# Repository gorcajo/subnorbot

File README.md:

# Subnorbot

In 2013 two friends and me participated in a robot-sumo contest (Alcabot) while we were still students.

This repository contains the soruce and hardware schematics we used to develop the robot. It is based on Arduino Uno.

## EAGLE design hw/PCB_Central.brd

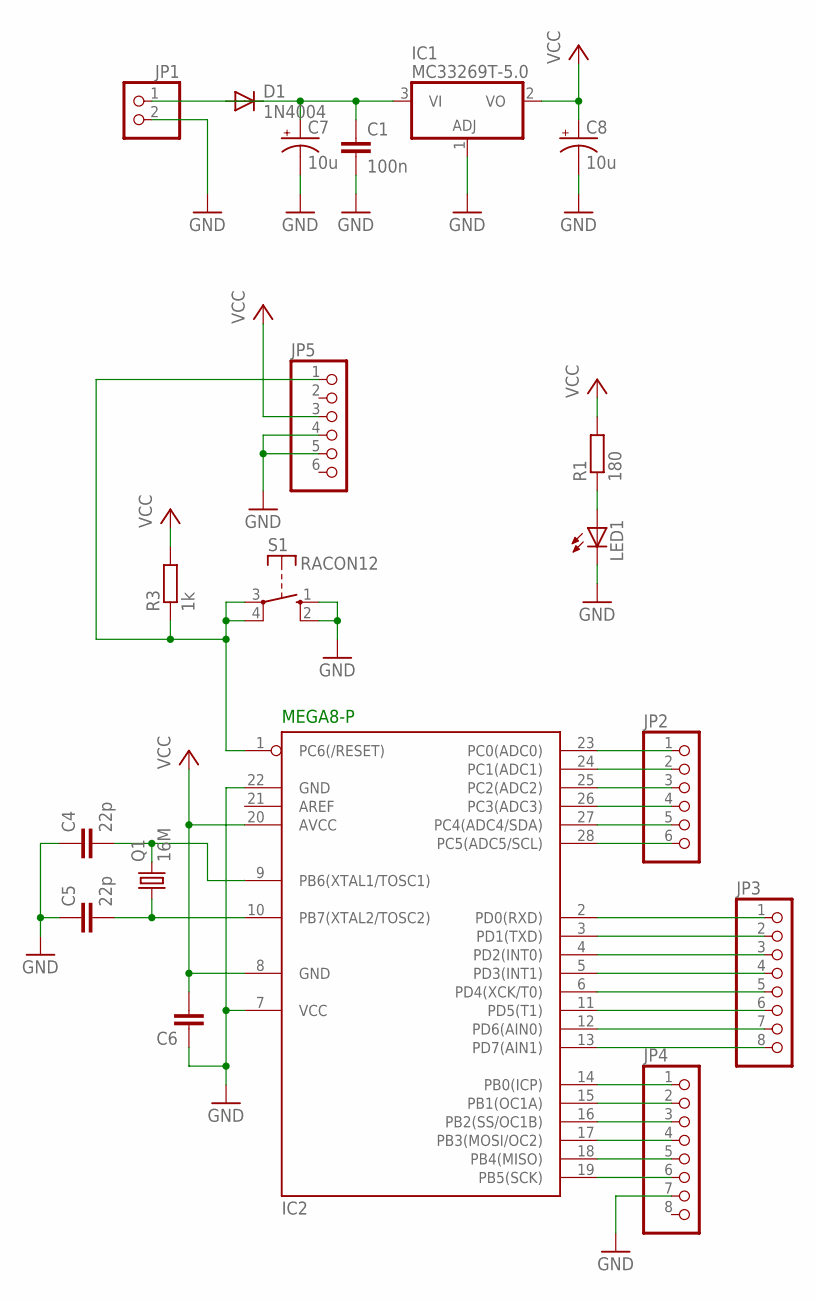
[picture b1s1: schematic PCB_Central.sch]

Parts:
C1: 100n; C2.5-3
C4, C5: 22p; C2.5-3
C6: C2,5-3; C2.5-3
C7, C8: 10u; E5-13
D1: 1N4004; DO41-10
IC1: MC33269T-5.0; TO220V
IC2: MEGA8-P; DIL28-3
JP1: PINHD-1X2; 1X02
JP2, JP5: PINHD-1X6; 1X06
JP3, JP4: PINHD-1X8; 1X08
LED1: LED5MM
Q1: 16M; HC49/S
R1: 180; 0207/12
R3: 1k; 0207/12
S1: RACON12

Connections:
GND: C1.2, C4.1, C5.1, C6.1, C7.-, C8.-, IC1.1 (ADJ), IC2.7 (VCC), IC2.22 (GND), JP1.2, JP4.7, JP5.4, JP5.5, LED1.K (C), S1.1 (S), S1.2 (S)
unnamed: LED1.A, R1.1
unnamed: C1.1, C7.+, D1.A, D1.C, IC1.3 (VI), JP1.1
unnamed: IC2.1 (PC6(/RESET)), JP5.1, R3.1, S1.3, S1.4
unnamed: IC2.14 (PB0(ICP)), JP4.1
unnamed: IC2.15 (PB1(OC1A)), JP4.2
unnamed: IC2.16 (PB2(SS/OC1B)), JP4.3
unnamed: IC2.17 (PB3(MOSI/OC2)), JP4.4
unnamed: IC2.18 (PB4(MISO)), JP4.5
unnamed: IC2.19 (PB5(SCK)), JP4.6
unnamed: C4.2, IC2.9 (PB6(XTAL1/TOSC1)), Q1.2
unnamed: C5.2, IC2.10 (PB7(XTAL2/TOSC2)), Q1.1
unnamed: IC2.23 (PC0(ADC0)), JP2.1
unnamed: IC2.24 (PC1(ADC1)), JP2.2
unnamed: IC2.25 (PC2(ADC2)), JP2.3
unnamed: IC2.26 (PC3(ADC3)), JP2.4
unnamed: IC2.27 (PC4(ADC4/SDA)), JP2.5
unnamed: IC2.28 (PC5(ADC5/SCL)), JP2.6
unnamed: IC2.2 (PD0(RXD)), JP3.1
unnamed: IC2.3 (PD1(TXD)), JP3.2
unnamed: IC2.4 (PD2(INT0)), JP3.3
unnamed: IC2.5 (PD3(INT1)), JP3.4
unnamed: IC2.6 (PD4(XCK/T0)), JP3.5
unnamed: IC2.11 (PD5(T1)), JP3.6
unnamed: IC2.12 (PD6(AIN0)), JP3.7
unnamed: IC2.13 (PD7(AIN1)), JP3.8
VCC: C6.2, C8.+, IC1.2 (VO), IC2.8 (GND), IC2.20 (AVCC), JP5.3, R1.2, R3.2

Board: 2 copper layers, 19 parts (0 on the bottom side), 27 nets, no tracks yet.

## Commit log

2013-03-07 Commit inicial.
2013-03-07 Prueba 1
2013-03-07 Prueba 2
2013-03-07 Prueba 3
2013-03-11 Prueba 4
2013-03-11 Prueba 5
2013-03-11 cacaculopedopis
2013-03-11 mi pene
2013-03-11 Limpieza de ficheros guarros para pruebas.
2013-03-18 - Nueva carpeta de recursos donde meter links, instrucciones, manuales, herramientas... - Fichero de texto con las instrucciones para usar el programador AVRISP MKII de Atmel con Arduino.
2013-03-18 Agregados los drivers para Windows del AVRISPmk2 en /recursos/.
2013-03-18 Pequeña nota en el uso del AVRISPmk2.
2013-03-18 añadido datasheet atmega328p
2013-03-19 - Nueva carpeta de /recursos/ con lo siguiente: -- Añadida una propuesta para la estructura sw. -- Añadida una propuesta acerca de estándares de programación. - Añadido un fichero sobre links de inte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
2013-03-19 - Nueva carpeta, /doc/ - Propuesta de estructura de sw en /doc/ - Propuesta de estándares de programacion en /doc/ - Fichero con links de interes en /recursos/
2013-03-21 Estructura base del SW. - Descrita en subnorbot.h la estructura sw que existe hasta el momento. - Implementado el metodo setSnifers() en sense.cpp. - Modificado sw.ino para incluir las librerias que 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
2013-03-24 Método SubnorBot.initializa() finalizado, a falta de más operaciones que realizar o nuevas propiedades que inicializar. Creadas nuevas macros en subnorbot.h: constantes acerca del hardware, como los 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
2013-03-24 Método SubnorBot.move() terminado. Añadido nuevo convenio en /doc/estandaresProgramacion.txt Mejorado SubnorBot.initialize() Añadidos algunos prototipos de funciones en resolve.cpp
2013-03-24 Ahora las funciones de la IA utilizadas en resolve.cpp son métodos dentro de la clase SubnorBot. A partir de ahora si fuera necesario añadir más métodos se hará dentro de su "apartado" correspondient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
2013-03-24 Implementado el esqueleto de una primera version de la maquina de estados de la IA en resolve(). Implementados los métodos básicos de IA rotate(), pivot(), approach() y charge(). Eliminación de algun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
2013-03-24 Nueva constante en subnorbot.h: ENGINES_SPEED_CORRECTION. Cambios menores.
2013-03-24 Mejorada la corrección de diferencia de velocidad de los motores. Cambios menores.
2013-03-26 nuevo commit
2013-03-29 resolve() terminado. Añadidas algunas constantes más (macros, realmente) en subnorbot.h Optimizado el codigo en move.cpp.
2013-04-01 Añadida documentación sobre la IA, en /doc/.
2013-04-01 Arreglado el PNG que describe la IA.
2013-04-01 Mejorada la máquina de estados de la IA.
2013-04-01 Ampliado resolve() con el nuevo estado: AVOIDING_EDGE. Mejorado el diagrama de estados de la IA. La propiedad Subnorbot.sniffers es ahora una union que contiene dos chars y un bitfield (struct) de ti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
2013-04-02 Eliminado el codigo relacionado con las interrupciones. Añadida una macro que habilita el modo test (#define TEST). Este modo habilita la comunicacion serie por el USB con el PC y lo emplea para real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
2013-04-02 Implementado el control del LED RGB que indica el estado de la IA. Modificado initialize() y resolve() para dar uso a esta nueva funcionalidad. El enum que define el estado de la IA ahora es un typed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
2013-04-02 Nuevas funcionalidades del modo test. Añadidos los comando 'e' y 's' para ver el estado de los motores y ele stado de la IA en modo test por serie. Cambios menores y optimizaciones.
2013-04-02 Nuevos comandos de test: 'o' para forzar detección del rival, 'x' para forzar pérdida del rival. Cambios menores relacionados con el modo test (métodos de subnorbot, sólo compilados en modo test). Co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
2013-04-02 Eliminado el comando de test 'e'. El comando de test 's' ahora indica el estado de los dos motores y de la IA simultáneamente. Cambios menores.
2013-04-02 Creados 4 nuevos comandos de test: '1', '3', '7' y '9', para forzar una conmutación en los estados de los siguelíneas SW, SE, NW y NE (ver en teclado numérico). El comando de test 's' ahora muestra e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
2013-04-02 esquema subnorbot 1.0
2013-04-02 fotolitos de la placa añadidos
2013-04-03 Pequeñas optimizaciones chorra.
2013-04-05 Control del LED RGB corregido y verificado. Modo test verificado.
2013-04-05 Correccion del sentido de los motores terminado (vale con tocar la correción de velocidad, si es negativo le invierte el sentido, asi que realmente ya estaba hecho xD)
2013-04-06 Eliminadas y cambiadas las propiedades de Subnorbot relacionadas con los siguelíneas, que ahora son 3. Añadido un nuevo bit en el struct de los siguelíneas para indicar que se está realizando un repo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
2013-04-06 IA mejorada: agregadas maniobras de alejamiento del borde. El modo test ahora puede recibir varios comandos encadenados. Mejoras menores al modo test. Cambios menores
2013-04-06 Mejoras de IA.
2013-04-06 Agregadas las funciones de los sensores. Primera versión candidata.
2013-04-07 Añadida funcionalidad para parar completamente los motores.
2013-04-07 Bajada la velocidad de giro en searching y refinding al 25%.
2013-04-08 hola
2013-04-10 Versión final del software para el Alcabot 2013.
